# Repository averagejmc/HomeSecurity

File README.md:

# HomeSecurity 

A small local home security system that:

* receives sensor data via **MQTT**
* shows a real-time dashboard using **Flask + SocketIO**
* logs hourly snapshots to a **SQLite** database
* sends notifications through **Telegram Bot API**

The app runs at **[http://localhost:5000](http://localhost:5000)**.

---

## Requirements

* Python 3.10+
* **uv** (for virtualenv + dependency management)
* Mosquitto (or any MQTT broker at `localhost:1883`)
* Telegram bot token stored in an environment variable
  `TELEGRAM_TOKEN=<your token>`

---

## Installation

### 1. Create and activate the virtual environment

```bash
uv venv
source .venv/bin/activate   # Linux/macOS
```

Windows PowerShell:

```powershell
.\.venv\Scripts\Activate.ps1
```

### 2. Install all dependencies

```bash
uv sync
```

---

## Configure Telegram

For this project, we included the bot token in the code.
However, it is recommended to use environment variables 
instead for API and bot tokens.

Set the bot token as an environment variable:

Linux/macOS:

```bash
export TELEGRAM_TOKEN="your-token"
```

Windows PowerShell:

```powershell
setx TELEGRAM_TOKEN "your-token"
```

---

## Running the App

### 1. Start the MQTT broker

```bash
mosquitto
```

### 2. Run the web server

```bash
uv run webapp.py
```

Then open:

```
http://localhost:5000
```

---

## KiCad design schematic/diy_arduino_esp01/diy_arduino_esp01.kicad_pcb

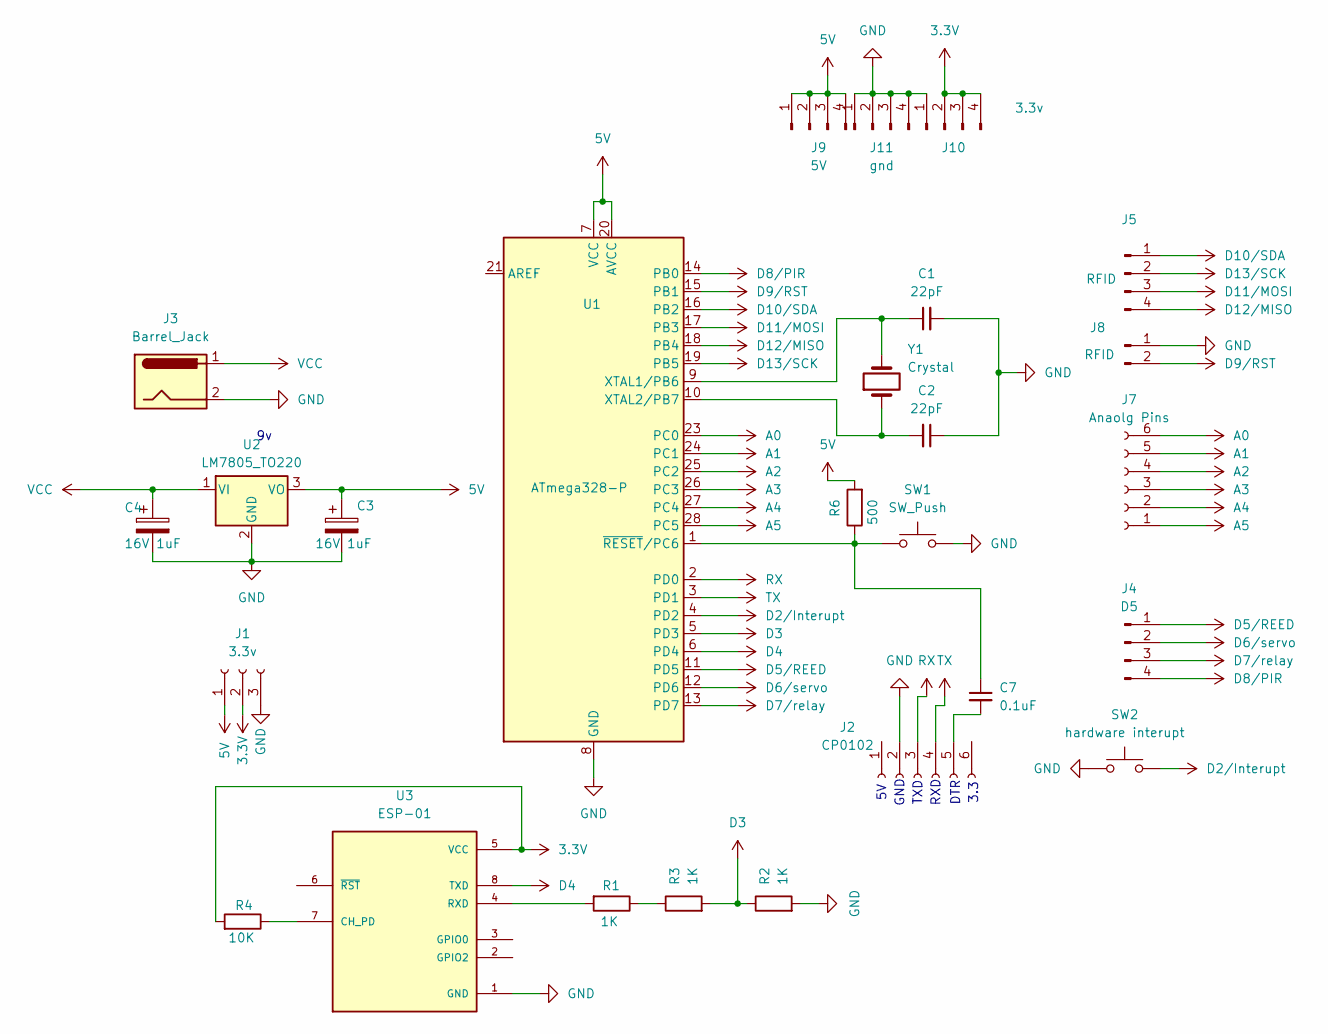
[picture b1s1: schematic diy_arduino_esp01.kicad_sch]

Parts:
C1, C2: 22pF; C_Disc_D5.0mm_W2.5mm_P5.00mm
C3, C4: 16V 1uF; CP_Radial_D5.0mm_P2.00mm
C7: 0.1uF; C_Disc_D5.0mm_W2.5mm_P5.00mm
J1: 3.3v; PinSocket_1x03_P2.54mm_Vertical
J2: CP0102; PinSocket_1x06_P2.54mm_Vertical
J3: Barrel_Jack; BarrelJack_Horizontal
J4: D5; PinSocket_1x04_P2.54mm_Vertical
J5: RFID; PinSocket_1x04_P2.54mm_Vertical
J7: Anaolg Pins; PinSocket_1x06_P2.54mm_Vertical
J8: RFID; PinSocket_1x02_P2.54mm_Vertical
J9: 5V; PinSocket_1x04_P2.54mm_Vertical
J10: 3.3v; PinSocket_1x04_P2.54mm_Vertical
J11: gnd; PinSocket_1x04_P2.54mm_Vertical
R1, R2, R3: 1K; R_Axial_DIN0207_L6.3mm_D2.5mm_P10.16mm_Horizontal
R4: 10K; R_Axial_DIN0207_L6.3mm_D2.5mm_P10.16mm_Horizontal
R6: 500; R_Axial_DIN0207_L6.3mm_D2.5mm_P10.16mm_Horizontal
SW1: SW_Push; SW_PUSH_6mm
SW2: hardware interupt; SW_PUSH_6mm
U1: ATmega328-P; DIP-28_W7.62mm
U2: LM7805_TO220; TO-220-3_Vertical
U3: ESP-01; MODULE_ESP-01; PARTREV 1.0
Y1: Crystal; Crystal_HC49-U_Vertical

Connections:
3.3V: J1.2, J10.2, J10.3, J10.4, R4.2, U3.5 (VCC)
5V: C3.1, J1.1, J9.1, J9.2, J9.3, J9.4, R6.2, U1.7 (VCC), U1.20 (AVCC), U2.3 (VO)
A0: J7.6, U1.23 (PC0)
A1: J7.5, U1.24 (PC1)
A2: J7.4, U1.25 (PC2)
A3: J7.3, U1.26 (PC3)
A4: J7.2, U1.27 (PC4)
A5: J7.1, U1.28 (PC5)
D2/Interupt: SW2.2, U1.4 (PD2)
D3: R2.1, R3.2, U1.5 (PD3)
D4: U1.6 (PD4), U3.8 (TXD)
D5/REED: J4.1, U1.11 (PD5)
D6/servo: J4.2, U1.12 (PD6)
D7/relay: J4.3, U1.13 (PD7)
D8/PIR: J4.4, U1.14 (PB0)
D9/RST: J8.2, U1.15 (PB1)
D10/SDA: J5.1, U1.16 (PB2)
D11/MOSI: J5.3, U1.17 (PB3)
D12/MISO: J5.4, U1.18 (PB4)
D13/SCK: J5.2, U1.19 (PB5)
GND: C1.2, C2.1, C3.2, C4.2, J1.3, J2.2, J3.2, J8.1, J10.1, J11.1, J11.2, J11.3, J11.4, R2.2, SW1.2, SW2.1, U1.8 (GND), U1.22 (GND), U2.2 (GND), U3.1 (GND)
unnamed: C7.2, J2.5
unnamed: R1.1, R3.1
unnamed: C1.1, U1.9 (XTAL1/PB6), Y1.2
unnamed: C2.2, U1.10 (XTAL2/PB7), Y1.1
unnamed: C7.1, R6.1, SW1.1, U1.1 (~RESET/PC6)
unnamed: R4.1, U3.7 (CH_PD)
unnamed: R1.2, U3.4 (RXD)
RX: J2.3, U1.2 (PD0)
TX: J2.4, U1.3 (PD1)
VCC: C4.1, J3.1, U2.1 (VI)

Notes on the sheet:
DTR
TXD
GND
RXD
3.3

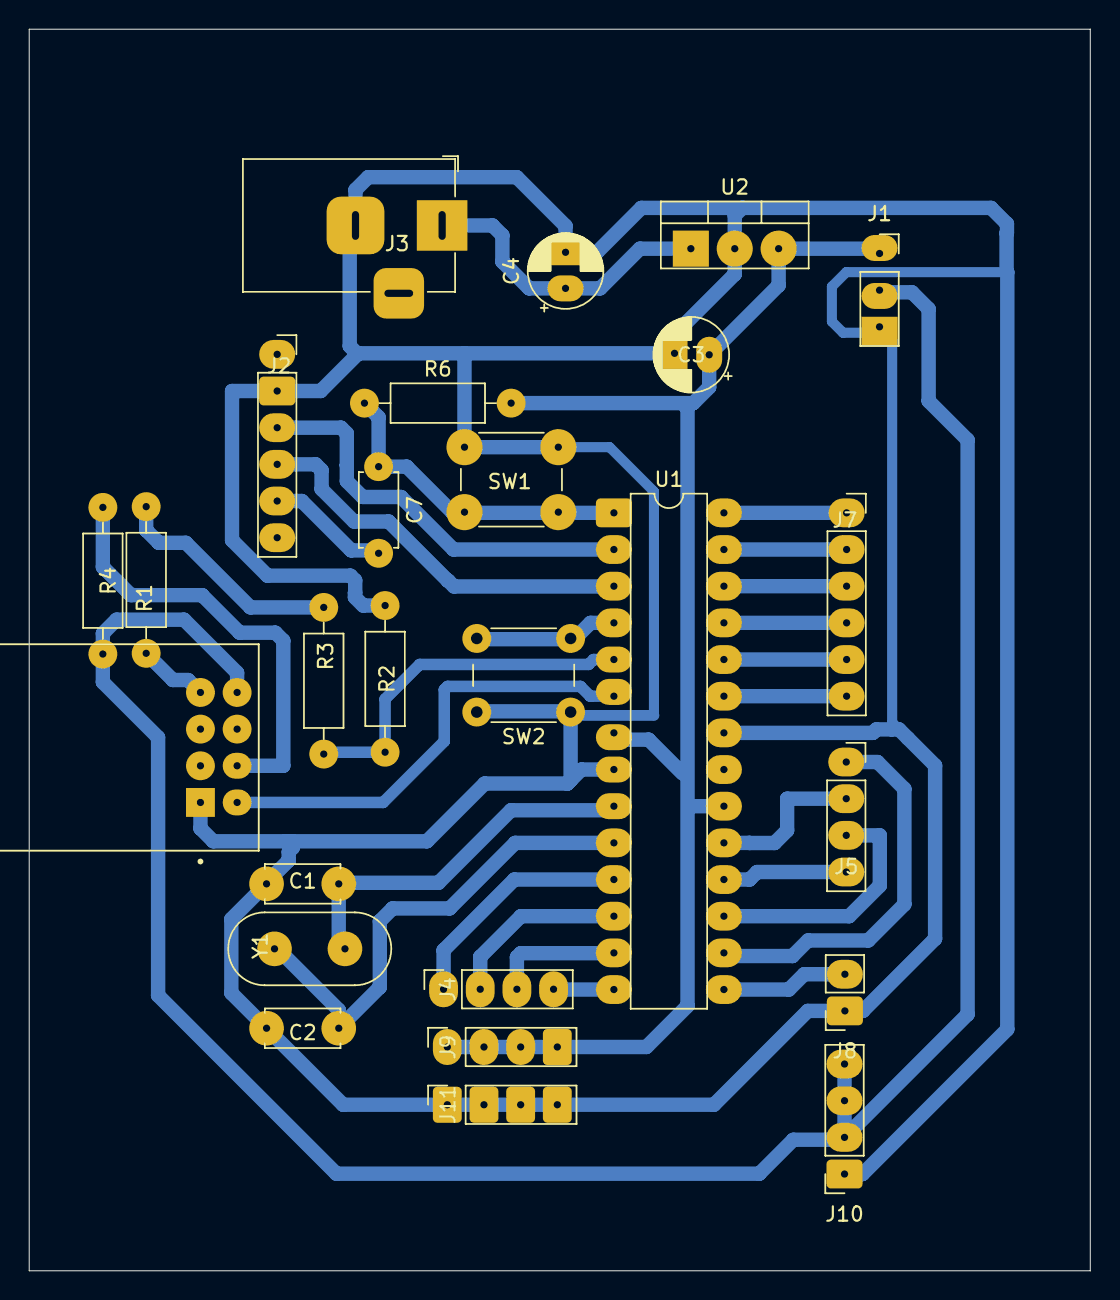
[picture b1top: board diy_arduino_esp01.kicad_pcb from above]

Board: 2 copper layers, 73.5 x 86.0 mm, 26 parts (0 on the bottom side), 31 nets.

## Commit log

2025-09-27 sept 28
2025-11-07 updated stuff to connect the log to the DB
2025-11-08 change from pip to uv
2025-11-08 Added Schematic for DIY Arduino with esp-01s
2025-11-08 Add schematic and routing images
2025-11-09 Wifi-Captive
2025-11-15 changed file structure and started on improving backend
2025-11-15 changed file structure and started on improving backend functionality
2025-11-16 added logs
2025-11-28 added arduino code
2025-11-28 added arduino code for real this time
2025-11-28 trying to make header on the arduino code
2025-11-29 improved frontend
2025-11-30 fixed commit conflicts
2025-11-30 code for arduino and esp01
2025-11-30 separated logic for arduino and esp01
2025-11-30 Added mode switching and Hardware Interrupt
2025-12-02 Added 3d models
2025-12-02 updated schematic
2025-12-07 final schematic
2025-12-07 updated image
2025-12-08 update arduino code and backend one last time
2025-12-08 minor updates
2025-12-08 updated logger to 10 mins interval
2025-12-09 updated maintenance tab
